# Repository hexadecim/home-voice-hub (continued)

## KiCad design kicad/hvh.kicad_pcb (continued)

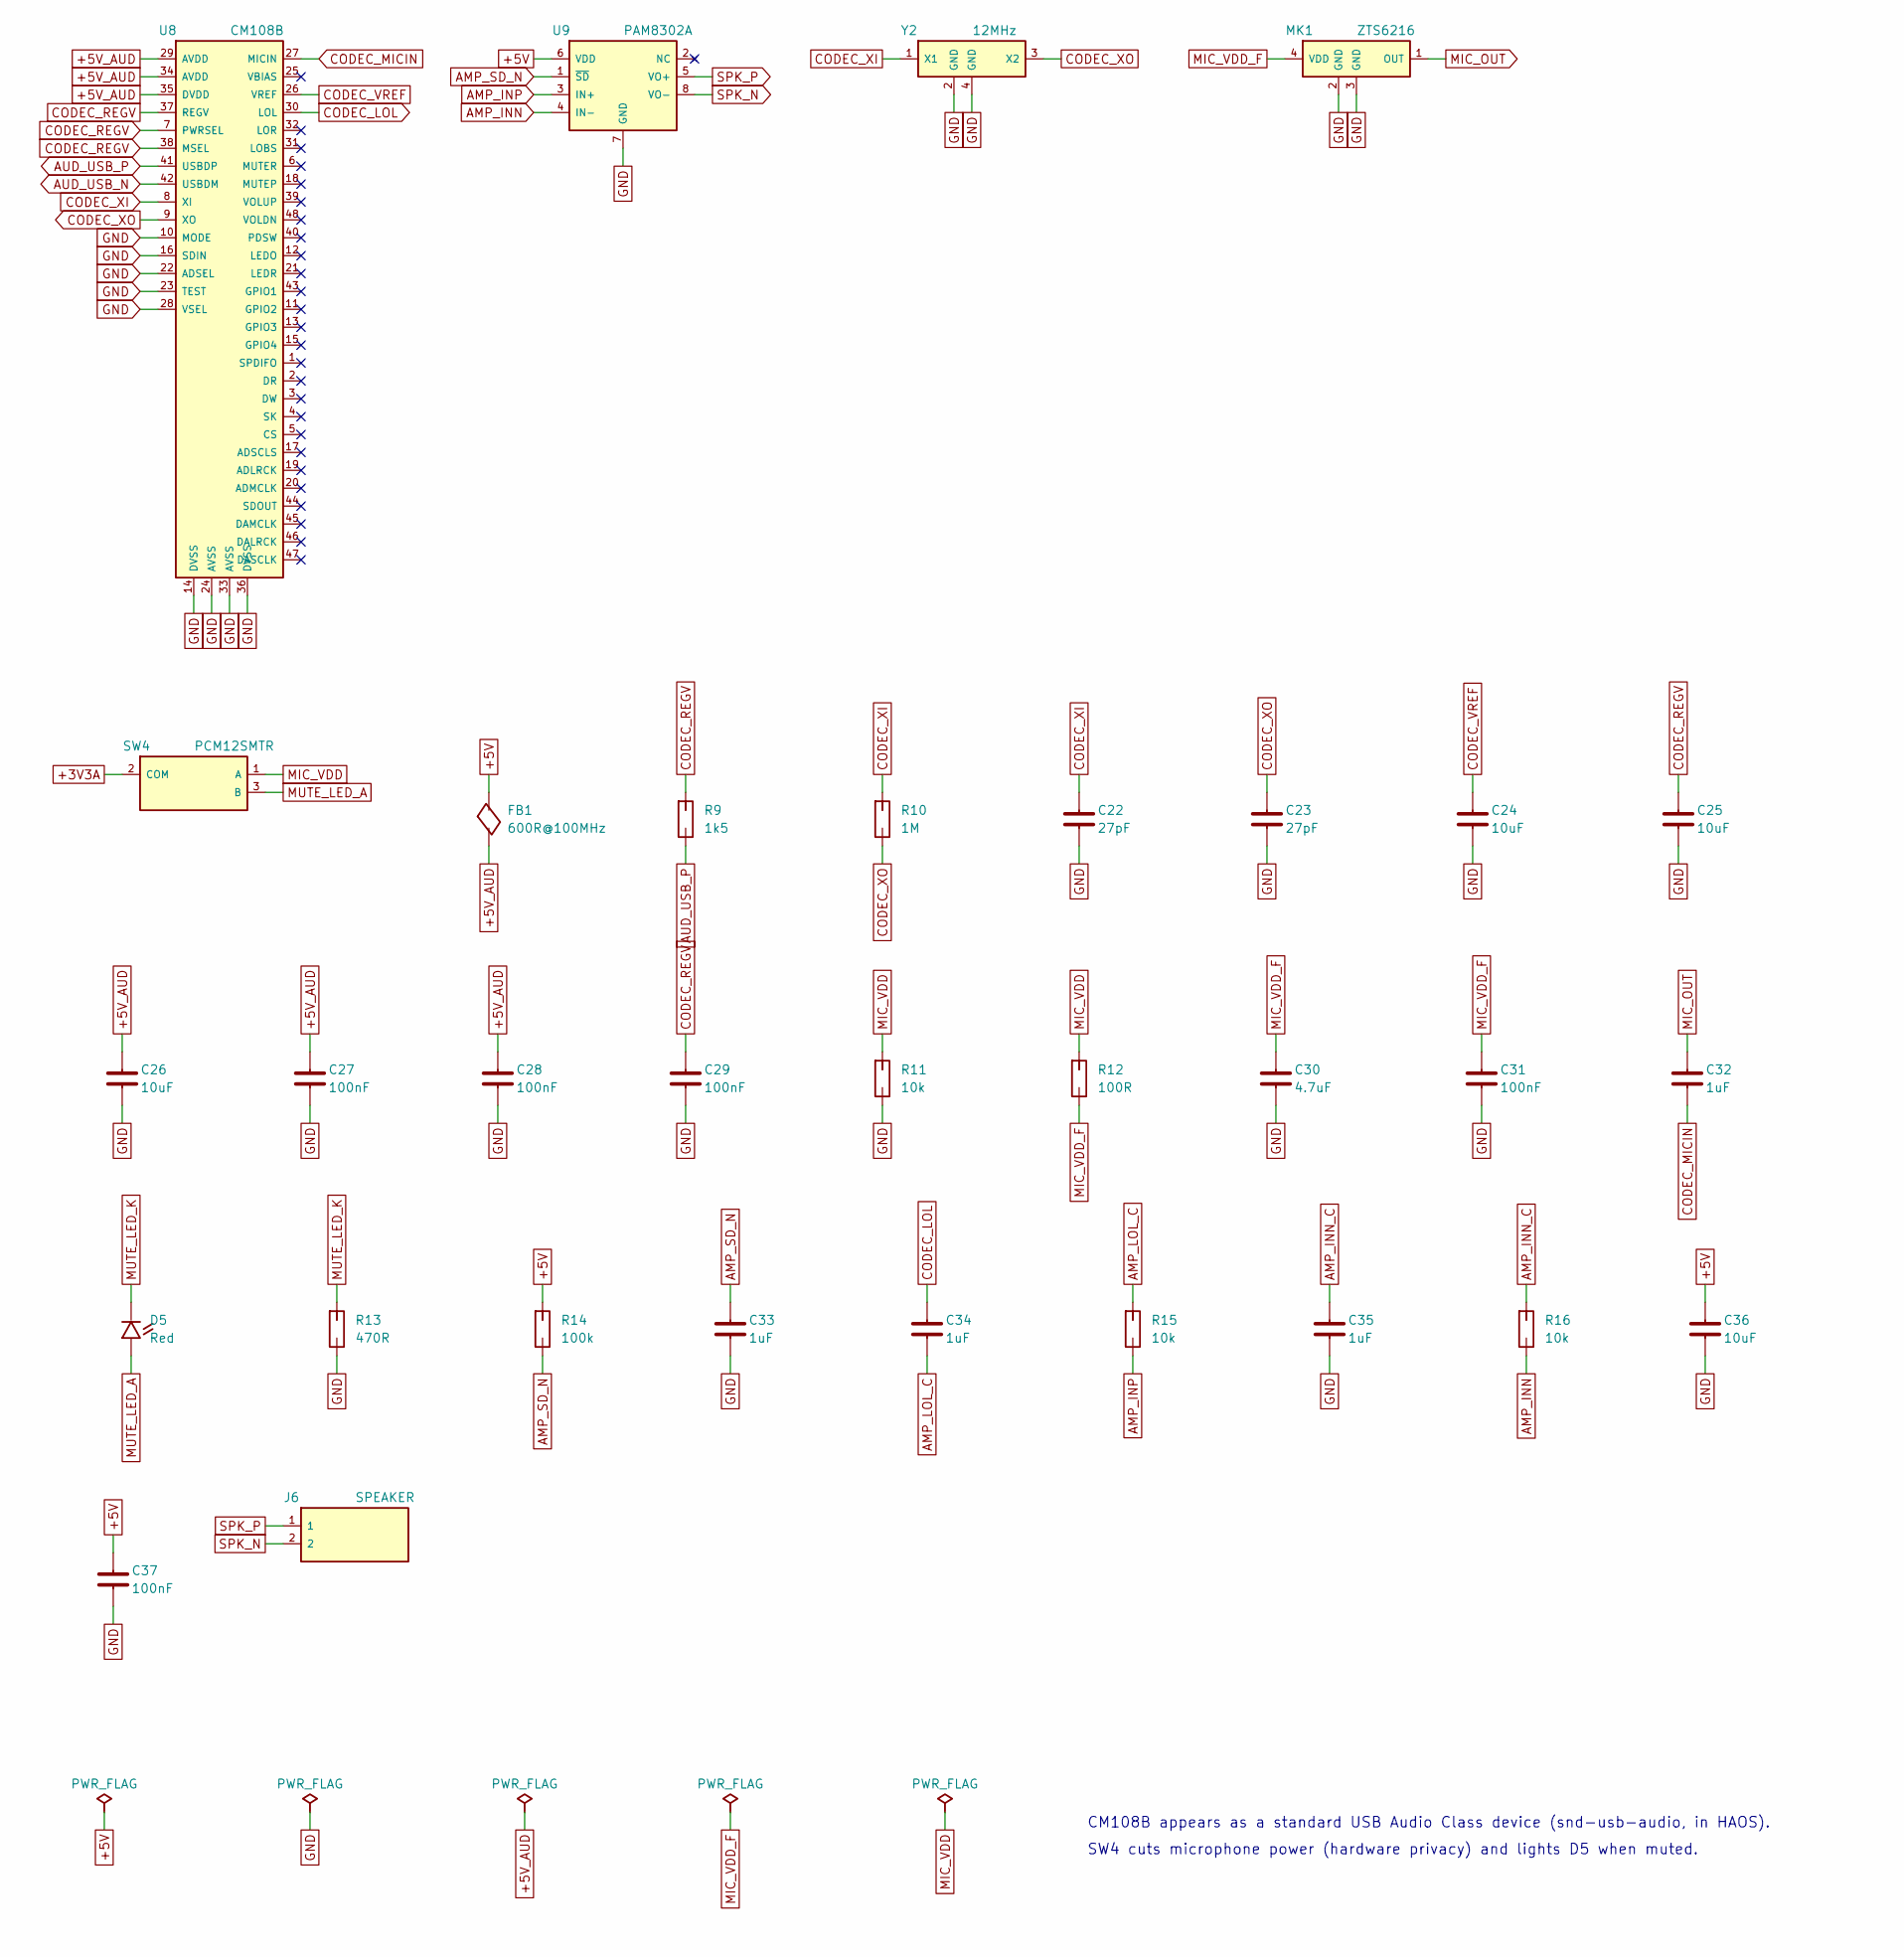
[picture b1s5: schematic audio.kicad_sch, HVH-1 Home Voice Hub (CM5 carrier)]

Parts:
C22, C23: 27pF; C_0402_1005Metric; MPN 0402CG270J500NT; LCSC C1557
C24, C25, C26: 10uF; C_0603_1608Metric; MPN CL10A106KP8NNNC; LCSC C19702
C27, C28, C29, C31, C37: 100nF; C_0402_1005Metric; MPN CL05B104KO5NNNC; LCSC C1525
C30: 4.7uF; C_0603_1608Metric; MPN CL10A475KO8NNNC; LCSC C19666
C32, C33, C34, C35: 1uF; C_0402_1005Metric; MPN CL05A105KA5NQNC; LCSC C52923
C36: 10uF; C_0805_2012Metric; MPN CL21A106KAYNNNE; LCSC C15850
D5: Red; LED_0603_1608Metric; MPN KT-0603R; LCSC C2286
FB1: 600R@100MHz; L_0603_1608Metric; MPN GZ1608D601TF; LCSC C1002
J6: SPEAKER; JST_PH_S2B-PH-K_1x02_P2.00mm_Horizontal; MPN S2B-PH-K-S(LF)(SN); LCSC C173752
MK1: ZTS6216; MIC_ZTS6216; MPN ZTS6216; LCSC C481302
R9: 1k5; R_0402_1005Metric; MPN 0402WGF1501TCE; LCSC C25867
R10: 1M; R_0402_1005Metric; MPN 0402WGF1004TCE; LCSC C26083
R11, R15, R16: 10k; R_0402_1005Metric; MPN 0402WGF1002TCE; LCSC C25744
R12: 100R; R_0402_1005Metric; MPN 0402WGF1000TCE; LCSC C25076
R13: 470R; R_0402_1005Metric; MPN 0402WGF4700TCE; LCSC C25117
R14: 100k; R_0402_1005Metric; MPN 0402WGF1003TCE; LCSC C25741
SW4: PCM12SMTR; SW_SPDT_PCM12; MPN PCM12SMTR; LCSC C221841
U8: CM108B; LQFP-48_7x7mm_P0.5mm; MPN CM108B; LCSC C371347
U9: PAM8302A; MSOP-8_3x3mm_P0.65mm; MPN PAM8302AASCR; LCSC C113367
Y2: 12MHz; Crystal_SMD_3225-4Pin_3.2x2.5mm; MPN X322512MSB4SI; LCSC C9002

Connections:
+3V3A: SW4.2 (COM); also elsewhere on the board
+5V: C36.1, C37.1, FB1.1, R14.1, U9.6 (VDD); also elsewhere on the board
+5V_AUD: C26.1, C27.1, C28.1, FB1.2, U8.29 (AVDD), U8.34 (AVDD), U8.35 (DVDD)
AMP_INN: R16.2, U9.4 (IN-)
AMP_INN_C: C35.1, R16.1
AMP_INP: R15.2, U9.3 (IN+)
AMP_LOL_C: C34.2, R15.1
AMP_SD_N: C33.1, R14.2, U9.1 (~SD)
AUD_USB_N: U8.42 (USBDM); also elsewhere on the board
AUD_USB_P: R9.2, U8.41 (USBDP); also elsewhere on the board
CODEC_LOL: C34.1, U8.30 (LOL)
CODEC_MICIN: C32.2, U8.27 (MICIN)
CODEC_REGV: C25.1, C29.1, R9.1, U8.7 (PWRSEL), U8.37 (REGV), U8.38 (MSEL)
CODEC_VREF: C24.1, U8.26 (VREF)
CODEC_XI: C22.1, R10.1, U8.8 (XI), Y2.1 (X1)
CODEC_XO: C23.1, R10.2, U8.9 (XO), Y2.3 (X2)
GND: C22.2, C23.2, C24.2, C25.2, C26.2, C27.2, C28.2, C29.2, C30.2, C31.2, C33.2, C35.2, C36.2, C37.2, MK1.2 (GND), MK1.3 (GND), R11.2, R13.2, U8.10 (MODE), U8.14 (DVSS), U8.16 (SDIN), U8.22 (ADSEL), U8.23 (TEST), U8.24 (AVSS), U8.28 (VSEL), U8.33 (AVSS), U8.36 (DVSS), U9.7 (GND), Y2.2 (GND), Y2.4 (GND); also elsewhere on the board
MIC_OUT: C32.1, MK1.1 (OUT)
MIC_VDD: R11.1, R12.1, SW4.1 (A)
MIC_VDD_F: C30.1, C31.1, MK1.4 (VDD), R12.2
MUTE_LED_A: D5.2, SW4.3 (B)
MUTE_LED_K: D5.1, R13.1
SPK_N: J6.2, U9.8 (VO-)
SPK_P: J6.1, U9.5 (VO+)

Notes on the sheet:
CM108B appears as a standard USB Audio Class device (snd-usb-audio, in HAOS).
SW4 cuts microphone power (hardware privacy) and lights D5 when muted.

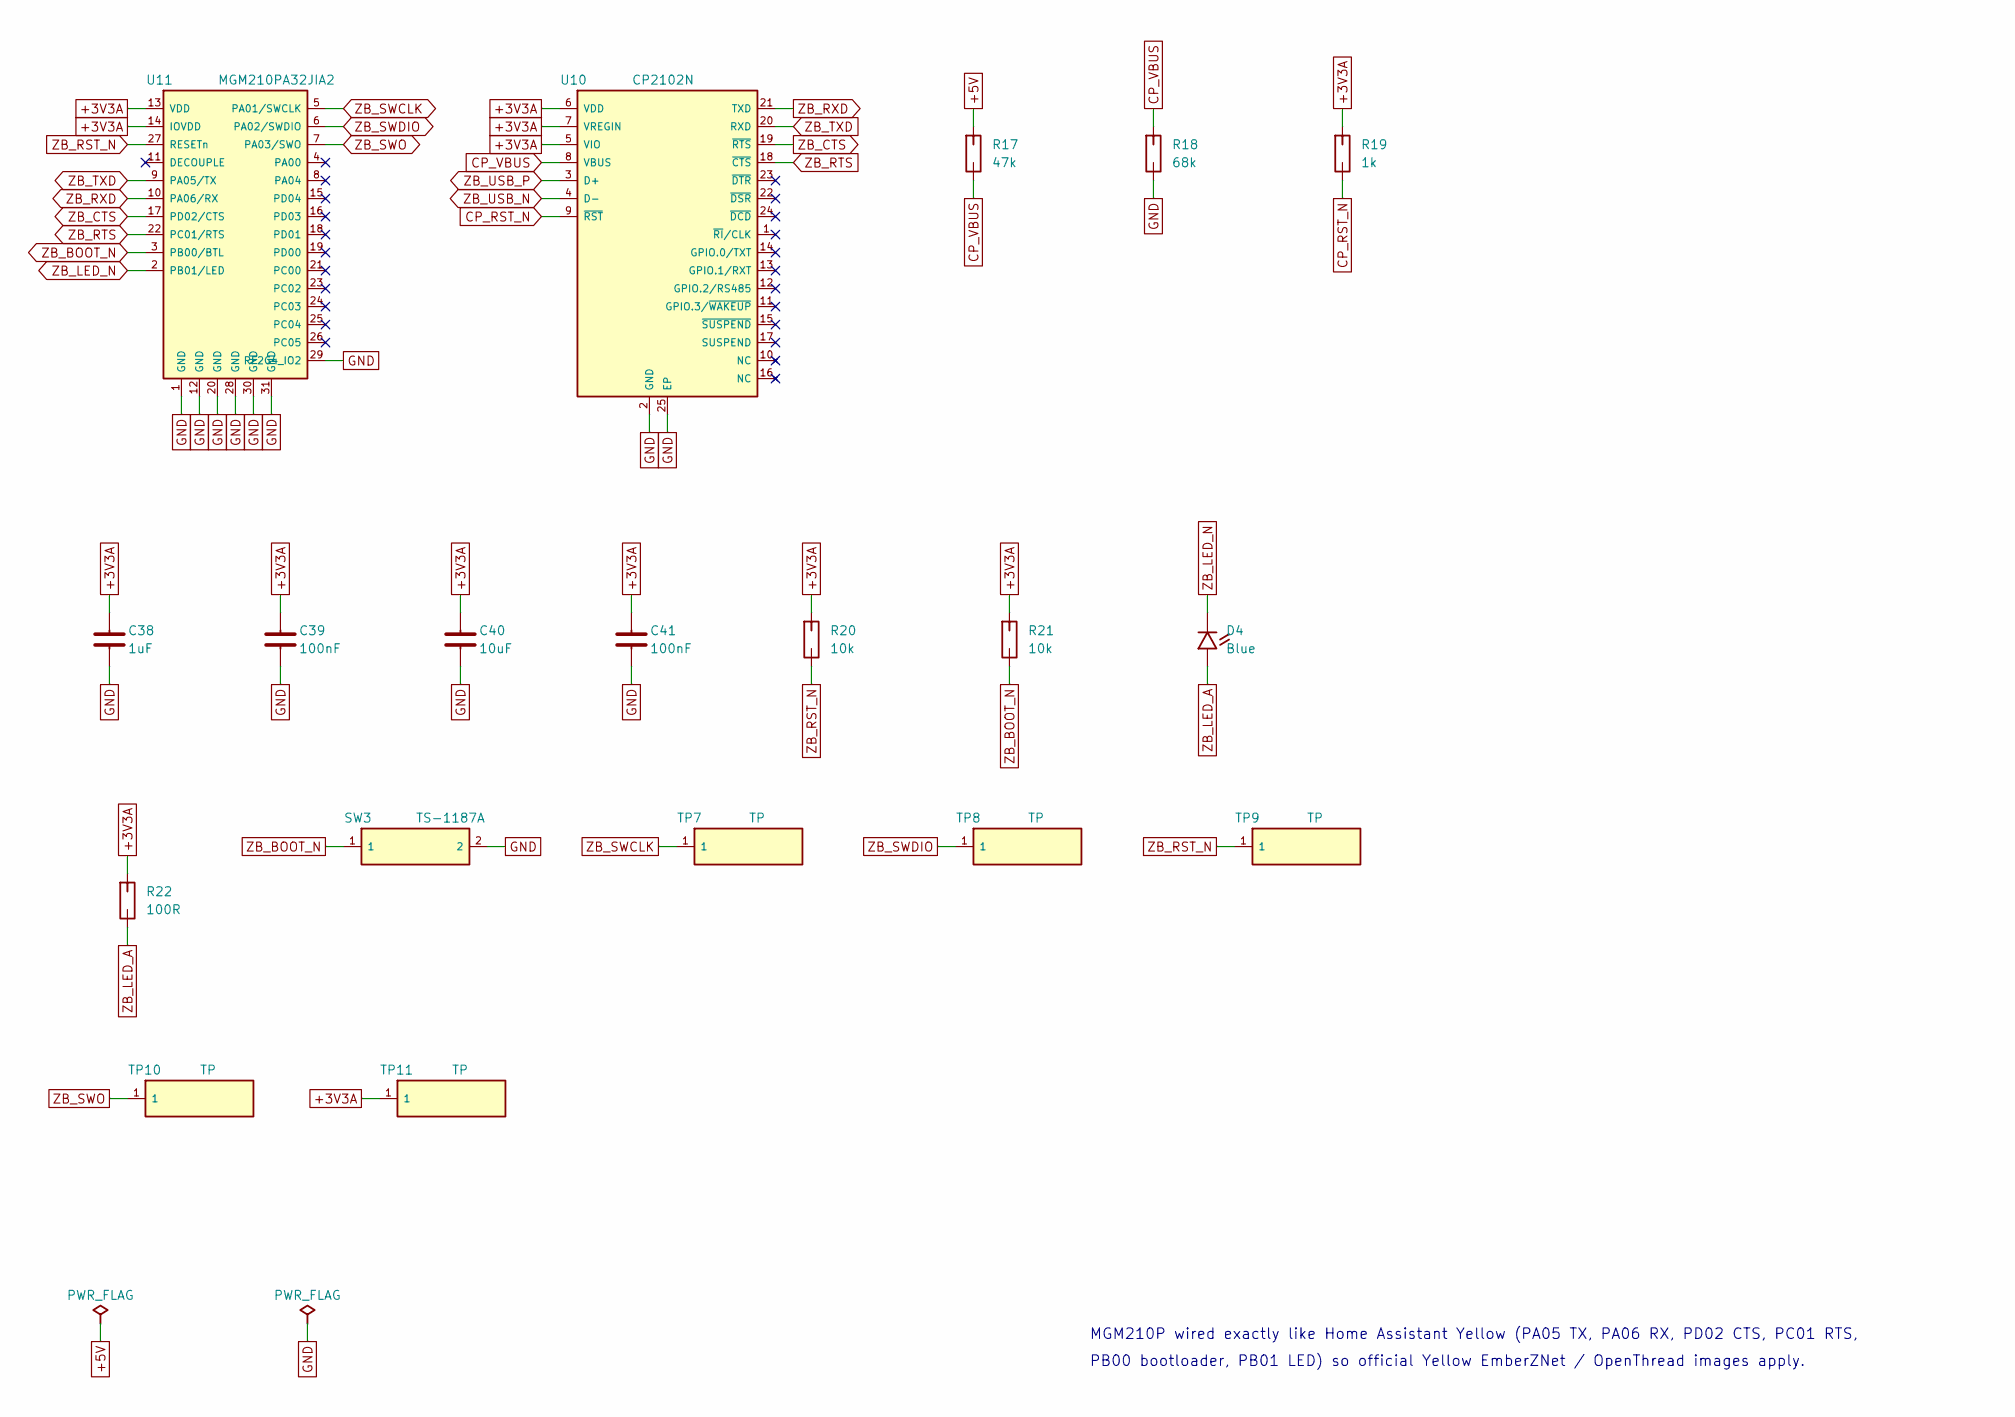
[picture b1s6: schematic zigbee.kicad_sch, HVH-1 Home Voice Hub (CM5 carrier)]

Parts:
C38: 1uF; C_0402_1005Metric; MPN CL05A105KA5NQNC; LCSC C52923
C39, C41: 100nF; C_0402_1005Metric; MPN CL05B104KO5NNNC; LCSC C1525
C40: 10uF; C_0603_1608Metric; MPN CL10A106KP8NNNC; LCSC C19702
D4: Blue; LED_0603_1608Metric; MPN XL-1608UBC-04; LCSC C965807
R17: 47k; R_0402_1005Metric; MPN 0402WGF4702TCE; LCSC C25792
R18: 68k; R_0402_1005Metric; MPN 0402WGF6802TCE; LCSC C36871
R19: 1k; R_0402_1005Metric; MPN 0402WGF1001TCE; LCSC C11702
R20, R21: 10k; R_0402_1005Metric; MPN 0402WGF1002TCE; LCSC C25744
R22: 100R; R_0402_1005Metric; MPN 0402WGF1000TCE; LCSC C25076
SW3: TS-1187A; SW_Push_1P1T_XKB_TS-1187A; MPN TS-1187A-B-A-B; LCSC C318884
TP7, TP8, TP9, TP10, TP11: TP; TestPoint_Pad_D1.0mm
U10: CP2102N; QFN-24-1EP_4x4mm_P0.5mm_EP2.6x2.6mm; MPN CP2102N-A02-GQFN24R; LCSC C969151
U11: MGM210PA32JIA2; SiliconLabs_MGM210P; MPN MGM210PA32JIA2; LCSC C1864147

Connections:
+3V3A: C38.1, C39.1, C40.1, C41.1, R19.1, R20.1, R21.1, R22.1, TP11.1, U10.5 (VIO), U10.6 (VDD), U10.7 (VREGIN), U11.13 (VDD), U11.14 (IOVDD); also elsewhere on the board
+5V: R17.1; also elsewhere on the board
CP_RST_N: R19.2, U10.9 (~RST)
CP_VBUS: R17.2, R18.1, U10.8 (VBUS)
GND: C38.2, C39.2, C40.2, C41.2, R18.2, SW3.2, U10.2 (GND), U10.25 (EP), U11.1 (GND), U11.12 (GND), U11.20 (GND), U11.28 (GND), U11.29 (RF2G4_IO2), U11.30 (GND), U11.31 (GND); also elsewhere on the board
ZB_BOOT_N: R21.2, SW3.1, U11.3 (PB00/BTL)
ZB_CTS: U10.19 (~RTS), U11.17 (PD02/CTS)
ZB_LED_A: D4.2, R22.2
ZB_LED_N: D4.1, U11.2 (PB01/LED)
ZB_RST_N: R20.2, TP9.1, U11.27 (RESETn)
ZB_RTS: U10.18 (~CTS), U11.22 (PC01/RTS)
ZB_RXD: U10.21 (TXD), U11.10 (PA06/RX)
ZB_SWCLK: TP7.1, U11.5 (PA01/SWCLK)
ZB_SWDIO: TP8.1, U11.6 (PA02/SWDIO)
ZB_SWO: TP10.1, U11.7 (PA03/SWO)
ZB_TXD: U10.20 (RXD), U11.9 (PA05/TX)
ZB_USB_N: U10.4 (D-); also elsewhere on the board
ZB_USB_P: U10.3 (D+); also elsewhere on the board

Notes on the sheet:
MGM210P wired exactly like Home Assistant Yellow (PA05 TX, PA06 RX, PD02 CTS, PC01 RTS,
PB00 bootloader, PB01 LED) so official Yellow EmberZNet / OpenThread images apply.

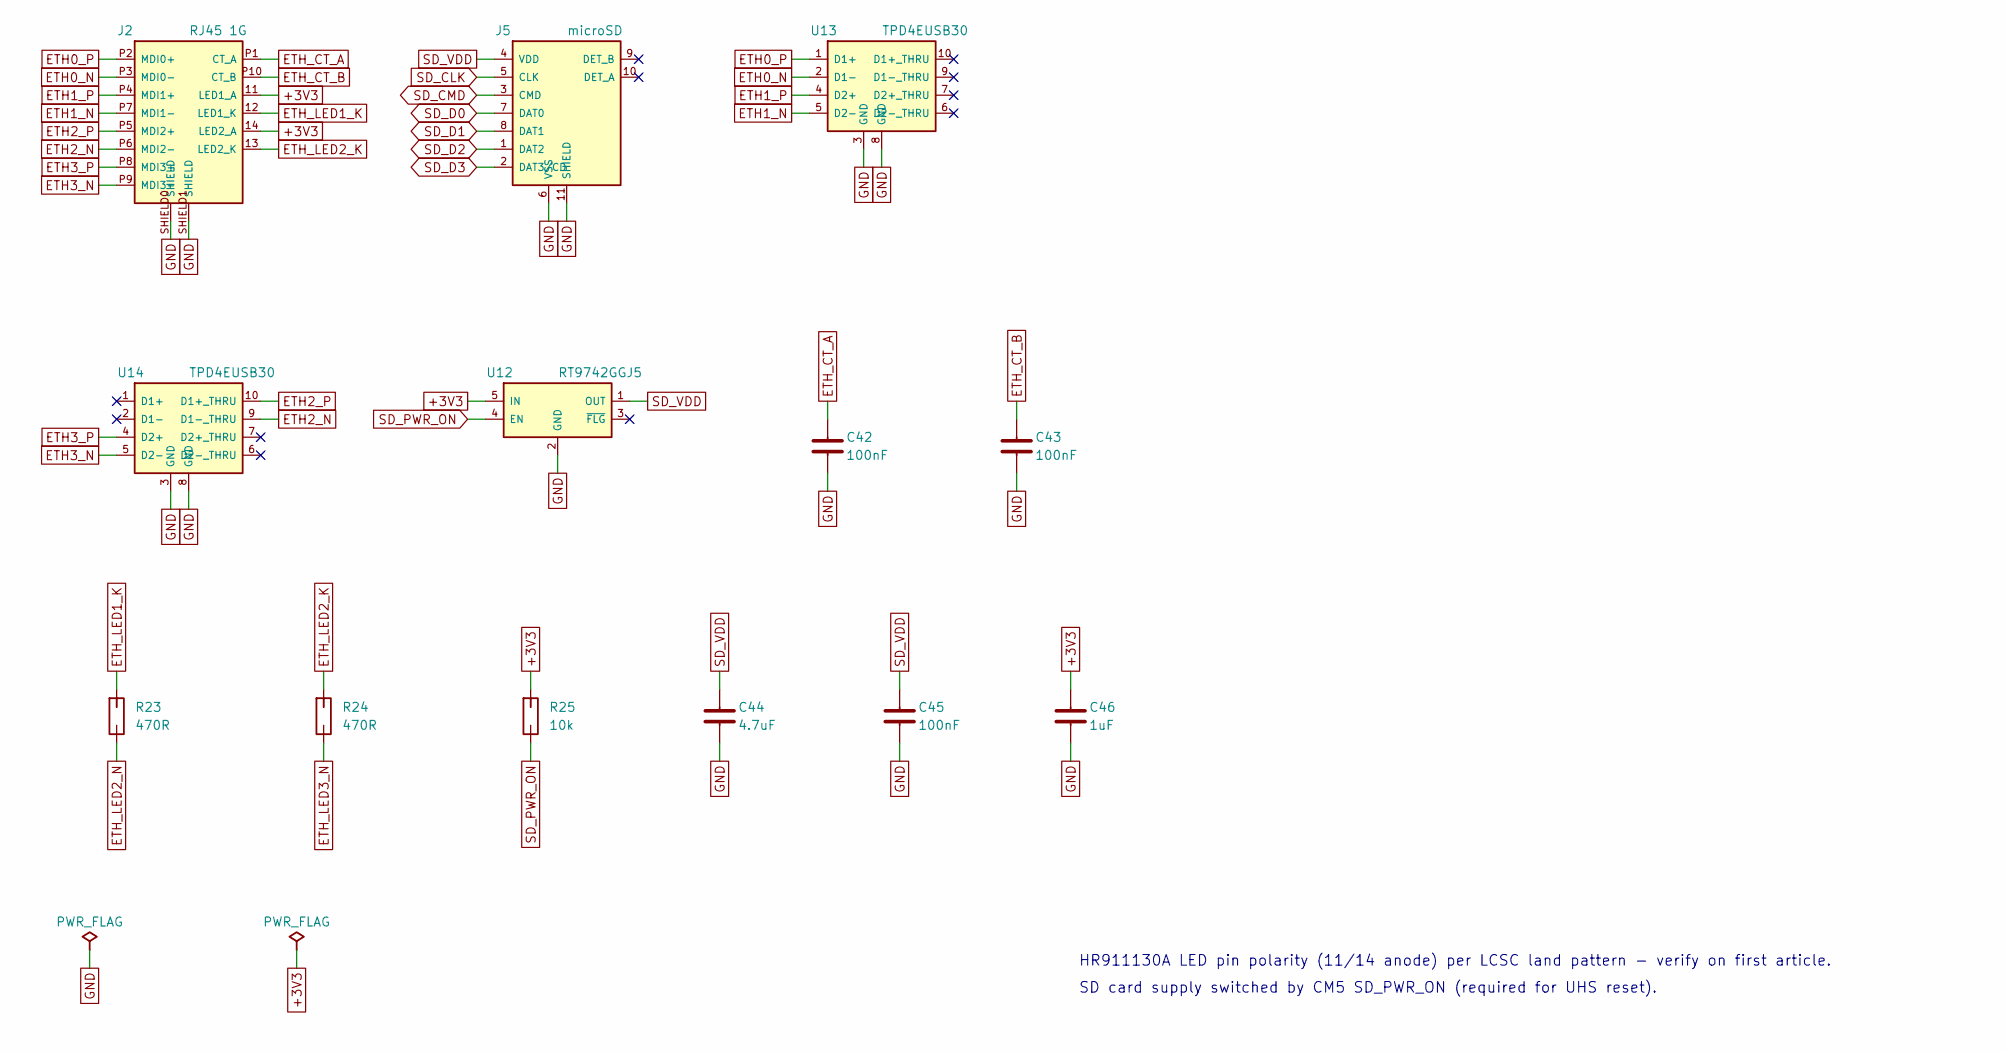
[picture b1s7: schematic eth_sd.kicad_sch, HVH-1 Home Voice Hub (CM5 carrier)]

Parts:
C42, C43, C45: 100nF; C_0402_1005Metric; MPN CL05B104KO5NNNC; LCSC C1525
C44: 4.7uF; C_0603_1608Metric; MPN CL10A475KO8NNNC; LCSC C19666
C46: 1uF; C_0402_1005Metric; MPN CL05A105KA5NQNC; LCSC C52923
J2: RJ45 1G; RJ45_HanRun_HR911130A; MPN HR911130A; LCSC C54408
J5: microSD; microSD_HC_Molex_104031-0811; MPN 1040310811; LCSC C585350
R23, R24: 470R; R_0402_1005Metric; MPN 0402WGF4700TCE; LCSC C25117
R25: 10k; R_0402_1005Metric; MPN 0402WGF1002TCE; LCSC C25744
U12: RT9742GGJ5; SOT-23-5; MPN RT9742GGJ5; LCSC C250547
U13, U14: TPD4EUSB30; USON-10_2.5x1.0mm_P0.5mm; MPN TPD4EUSB30DQAR; LCSC C90627

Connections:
+3V3: C46.1, J2.11 (LED1_A), J2.14 (LED2_A), R25.1, U12.5 (IN); also elsewhere on the board
ETH0_N: J2.P3 (MDI0-), U13.2 (D1-); also elsewhere on the board
ETH0_P: J2.P2 (MDI0+), U13.1 (D1+); also elsewhere on the board
ETH1_N: J2.P7 (MDI1-), U13.5 (D2-); also elsewhere on the board
ETH1_P: J2.P4 (MDI1+), U13.4 (D2+); also elsewhere on the board
ETH2_N: J2.P6 (MDI2-), U14.9 (D1-_THRU); also elsewhere on the board
ETH2_P: J2.P5 (MDI2+), U14.10 (D1+_THRU); also elsewhere on the board
ETH3_N: J2.P9 (MDI3-), U14.5 (D2-); also elsewhere on the board
ETH3_P: J2.P8 (MDI3+), U14.4 (D2+); also elsewhere on the board
ETH_CT_A: C42.1, J2.P1 (CT_A)
ETH_CT_B: C43.1, J2.P10 (CT_B)
ETH_LED1_K: J2.12 (LED1_K), R23.1
ETH_LED2_K: J2.13 (LED2_K), R24.1
ETH_LED2_N: R23.2; also elsewhere on the board
ETH_LED3_N: R24.2; also elsewhere on the board
GND: C42.2, C43.2, C44.2, C45.2, C46.2, J2.SHIELD0 (SHIELD), J2.SHIELD1 (SHIELD), J5.6 (VSS), J5.11 (SHIELD), U12.2 (GND), U13.3 (GND), U13.8 (GND), U14.3 (GND), U14.8 (GND); also elsewhere on the board
SD_CLK: J5.5 (CLK); also elsewhere on the board
SD_CMD: J5.3 (CMD); also elsewhere on the board
SD_D0: J5.7 (DAT0); also elsewhere on the board
SD_D1: J5.8 (DAT1); also elsewhere on the board
SD_D2: J5.1 (DAT2); also elsewhere on the board
SD_D3: J5.2 (DAT3/CD); also elsewhere on the board
SD_PWR_ON: R25.2, U12.4 (EN); also elsewhere on the board
SD_VDD: C44.1, C45.1, J5.4 (VDD), U12.1 (OUT); also elsewhere on the board

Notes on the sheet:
HR911130A LED pin polarity (11/14 anode) per LCSC land pattern - verify on first article.
SD card supply switched by CM5 SD_PWR_ON (required for UHS reset).

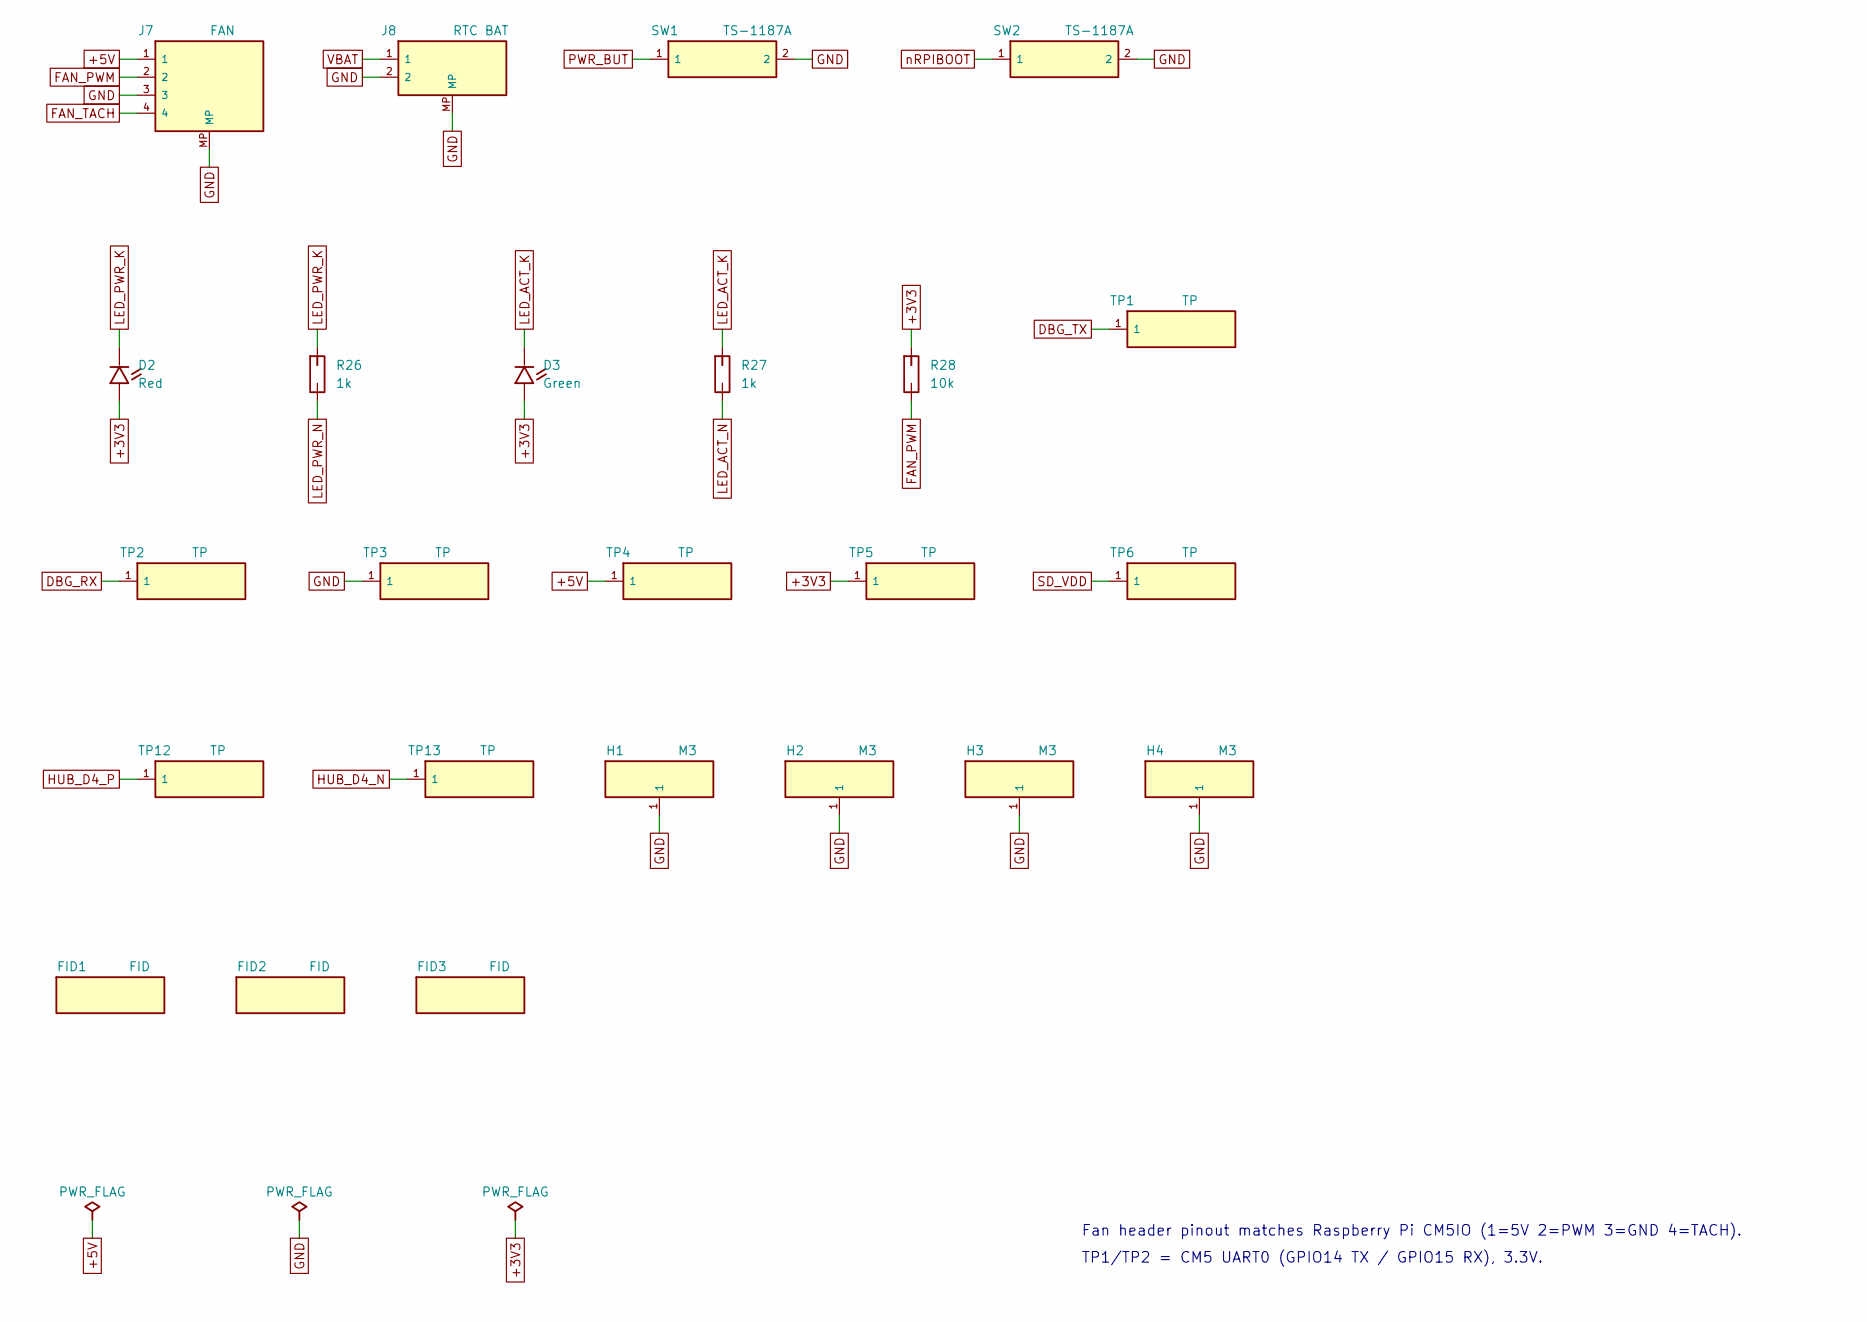
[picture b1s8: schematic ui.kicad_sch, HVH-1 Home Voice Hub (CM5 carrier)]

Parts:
D2: Red; LED_0603_1608Metric; MPN KT-0603R; LCSC C2286
D3: Green; LED_0603_1608Metric; MPN XL-1608UGC-04; LCSC C965804
FID1, FID2, FID3: FID; Fiducial_1mm_Mask2mm
H1, H2, H3, H4: M3; MountingHole_3.2mm_M3_Pad_Via
J7: FAN; JST_SH_SM04B-SRSS-TB_1x04-1MP_P1.00mm_Horizontal; MPN SM04B-SRSS-TB(LF)(SN); LCSC C160404
J8: RTC BAT; JST_SH_SM02B-SRSS-TB_1x02-1MP_P1.00mm_Horizontal; MPN SM02B-SRSS-TB(LF)(SN); LCSC C160402
R26, R27: 1k; R_0402_1005Metric; MPN 0402WGF1001TCE; LCSC C11702
R28: 10k; R_0402_1005Metric; MPN 0402WGF1002TCE; LCSC C25744
SW1, SW2: TS-1187A; SW_Push_1P1T_XKB_TS-1187A; MPN TS-1187A-B-A-B; LCSC C318884
TP1, TP2, TP3, TP4, TP5, TP6, TP12, TP13: TP; TestPoint_Pad_D1.0mm

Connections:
+3V3: D2.2, D3.2, R28.1, TP5.1; also elsewhere on the board
+5V: J7.1, TP4.1; also elsewhere on the board
DBG_RX: TP2.1; also elsewhere on the board
DBG_TX: TP1.1; also elsewhere on the board
FAN_PWM: J7.2, R28.2; also elsewhere on the board
FAN_TACH: J7.4; also elsewhere on the board
GND: H1.1, H2.1, H3.1, H4.1, J7.3, J7.MP, J8.2, J8.MP, SW1.2, SW2.2, TP3.1; also elsewhere on the board
HUB_D4_N: TP13.1; also elsewhere on the board
HUB_D4_P: TP12.1; also elsewhere on the board
LED_ACT_K: D3.1, R27.1
LED_ACT_N: R27.2; also elsewhere on the board
LED_PWR_K: D2.1, R26.1
LED_PWR_N: R26.2; also elsewhere on the board
PWR_BUT: SW1.1; also elsewhere on the board
SD_VDD: TP6.1; also elsewhere on the board
VBAT: J8.1; also elsewhere on the board
nRPIBOOT: SW2.1; also elsewhere on the board

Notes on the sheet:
Fan header pinout matches Raspberry Pi CM5IO (1=5V 2=PWM 3=GND 4=TACH).
TP1/TP2 = CM5 UART0 (GPIO14 TX / GPIO15 RX), 3.3V.

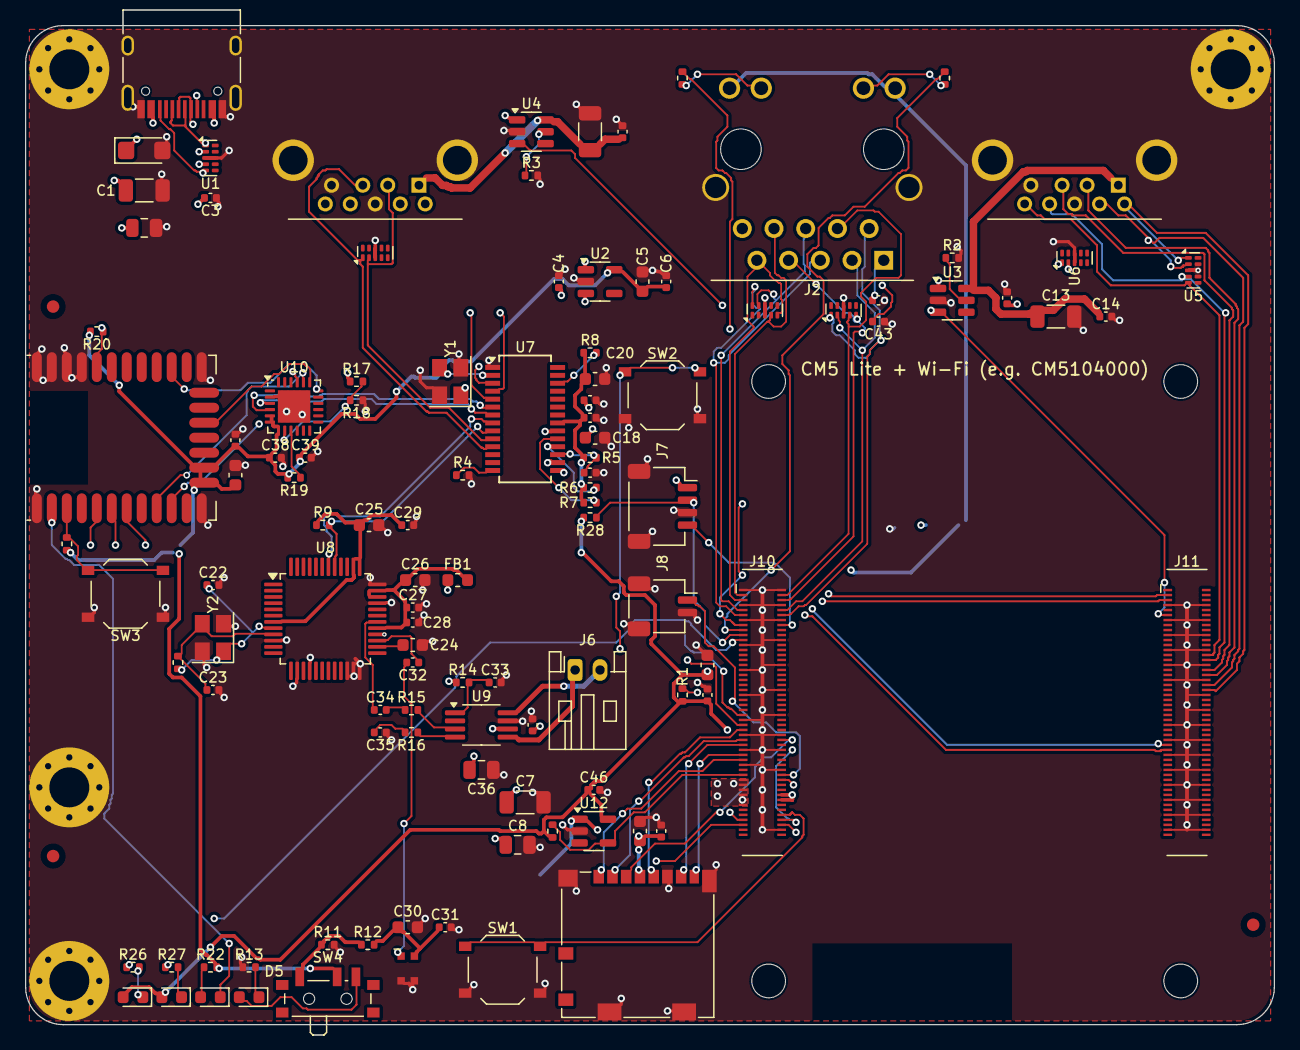
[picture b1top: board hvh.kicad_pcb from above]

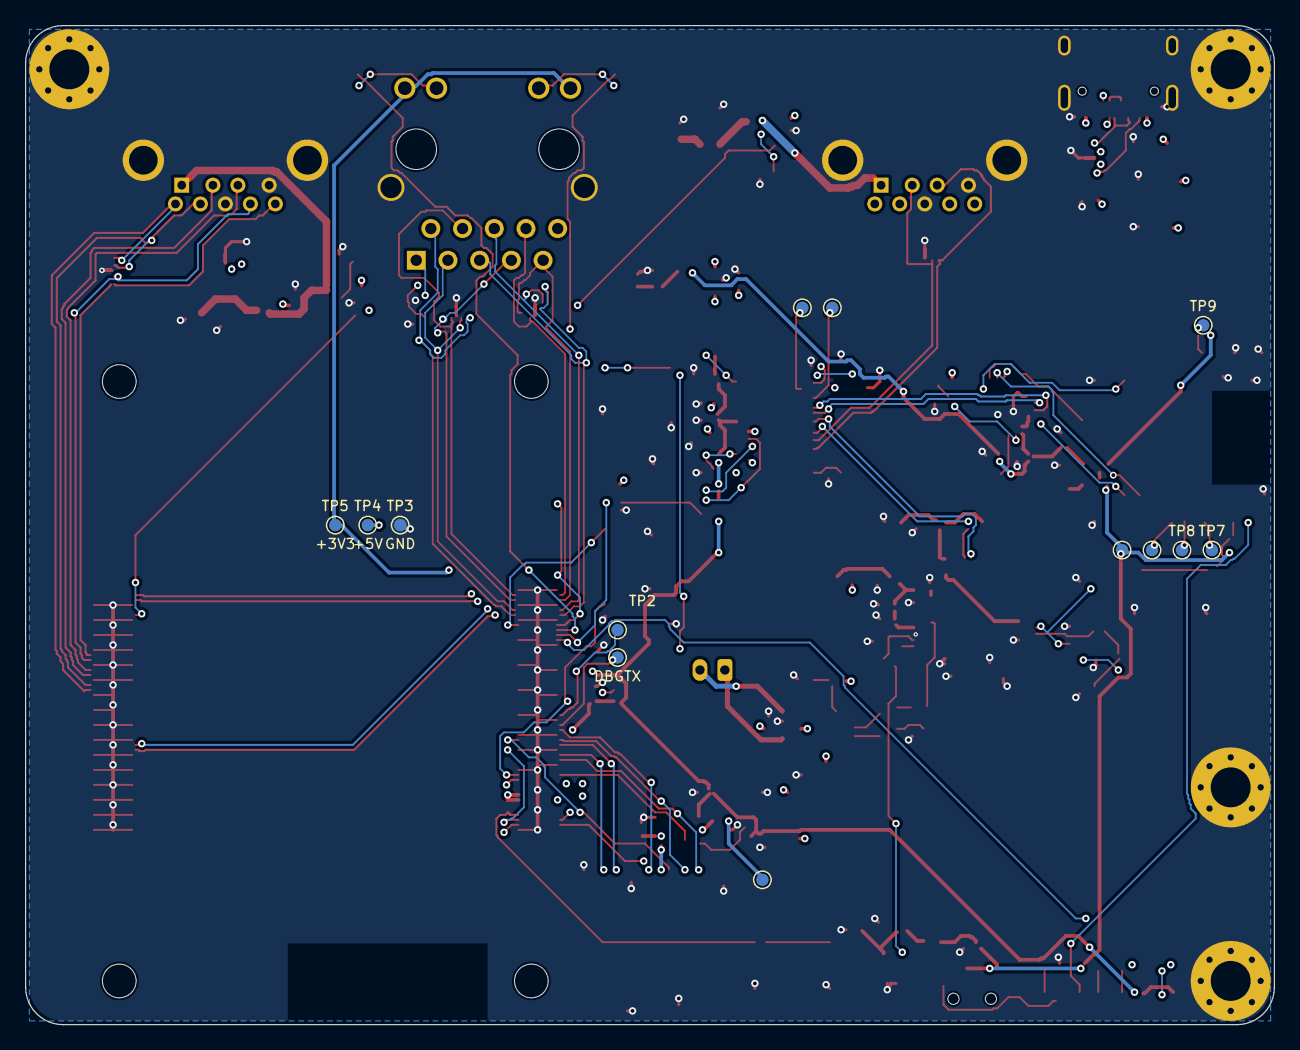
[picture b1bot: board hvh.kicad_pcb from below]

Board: 6 copper layers, 100.0 x 80.0 mm, 132 parts (13 on the bottom side), 103 nets.

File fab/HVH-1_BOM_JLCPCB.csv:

Comment,Designator,Footprint,LCSC Part #
USB-C PWR,J1,USB_C_Receptacle_HRO_TYPE-C-31-M-12,C165948
SMF5.0A,D1,D_SMF,C193402
47uF,"C1,C7,C13,C15",C_1206_3216Metric,C68361
22uF,C2,C_0805_2012Metric,C45783
100nF,"C3,C6,C11,C14,C16,C19,C21,C27,C28,C29,C31,C37,C39,C41,C42,C43,C45",C_0402_1005Metric,C1525
TPD4EUSB30,"U1,U5,U6,U13,U14,U15",USON-10_2.5x1.0mm_P0.5mm,C90627
TLV75533P,U2,SOT-23-5,C404027
1uF,"C4,C12,C17,C32,C33,C34,C35,C38,C46",C_0402_1005Metric,C52923
4.7uF,"C5,C10,C20,C30,C44",C_0603_1608Metric,C19666
DF40C-100DS,"J10,J11",CM5_DF40C-100DS-0.4V,C597931
0R,R1,R_0402_1005Metric,C17168
10uF,"C8,C36",C_0805_2012Metric,C15850
USB-A,"J3,J4",USB3_A_Amphenol_GSB311131HR,C473057
TPS2553,"U3,U4",SOT-23-6,C55266
26k1 1%,"R2,R3",R_0402_1005Metric,C155697
FE1.1s,U7,SSOP-28_3.9x9.9mm_P0.635mm,C9359
12MHz,"Y1,Y2",Crystal_SMD_3225-4Pin_3.2x2.5mm,C9002
2k7 1%,R4,R_0402_1005Metric,C25885
10k,"R5,R6,R7,R8,R11,R15,R16,R20,R21,R25,R28",R_0402_1005Metric,C25744
10uF,"C18,C24,C25,C26,C40",C_0603_1608Metric,C19702
600R@100MHz,FB1,L_0603_1608Metric,C1002
CM108B,U8,LQFP-48_7x7mm_P0.5mm,C371347
1k5,R9,R_0402_1005Metric,C25867
1M,R10,R_0402_1005Metric,C26083
27pF,"C22,C23",C_0402_1005Metric,C1557
PCM12SMTR,SW4,SW_SPDT_PCM12,C221841
100R,"R12,R22",R_0402_1005Metric,C25076
ZTS6216,MK1,MIC_ZTS6216,C481302
Red,"D2,D5",LED_0603_1608Metric,C2286
470R,"R13,R23,R24",R_0402_1005Metric,C25117
PAM8302A,U9,MSOP-8_3x3mm_P0.65mm,C113367
100k,R14,R_0402_1005Metric,C25741
SPEAKER,J6,JST_PH_S2B-PH-K_1x02_P2.00mm_Horizontal,C173752
CP2102N,U10,QFN-24-1EP_4x4mm_P0.5mm_EP2.6x2.6mm,C969151
47k,R17,R_0402_1005Metric,C25792
68k,R18,R_0402_1005Metric,C36871
1k,"R19,R26,R27",R_0402_1005Metric,C11702
MGM210PA32JIA2,U11,SiliconLabs_MGM210P,C1864147
Blue,D4,LED_0603_1608Metric,C965807
TS-1187A,"SW1,SW2,SW3",SW_Push_1P1T_XKB_TS-1187A,C318884
RJ45 1G,J2,RJ45_HanRun_HR911130A,C54408
microSD,J5,microSD_HC_Molex_104031-0811,C585350
RT9742GGJ5,U12,SOT-23-5,C250547
Green,D3,LED_0603_1608Metric,C965804
FAN,J7,JST_SH_SM04B-SRSS-TB_1x04-1MP_P1.00mm_Horizontal,C160404
RTC BAT,J8,JST_SH_SM02B-SRSS-TB_1x02-1MP_P1.00mm_Horizontal,C160402

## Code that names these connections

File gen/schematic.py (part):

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            "port 3 = Zigbee USB-UART, port 4 = test pads. FE1.1s has internal crystal load caps."],
    "audio": ["CM108B appears as a standard USB Audio Class device (snd-usb-audio, in HAOS).",
              "SW4 cuts microphone power (hardware privacy) and lights D5 when muted."],
    "zigbee": ["MGM210P wired exactly like Home Assistant Yellow (PA05 TX, PA06 RX, PD02 CTS, PC01 RTS,",
               "PB00 bootloader, PB01 LED) so official Yellow EmberZNet / OpenThread images apply."],
    "eth_sd": ["HR911130A LED pin polarity (11/14 anode) per LCSC land pattern - verify on first article.",
               "SD card supply switched by CM5 SD_PWR_ON (required for UHS reset)."],
    "ui": ["Fan header pinout matches Raspberry Pi CM5IO (1=5V 2=PWM 3=GND 4=TACH).",
           "TP1/TP2 = CM5 UART0 (GPIO14 TX / GPIO15 RX), 3.3V."],
}

def gen_root(papers):
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
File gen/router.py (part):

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ALL = list(range(NL))
OUTER_ONLY = {"USB3", "ETH", "USB3_FAT", "ETH_FAT", "VBUS", "SPK", "P5V"}   # USB2 may use In2 (stripline, 90R target)
PAIR_PITCH = 0.40
NOFAT = {"USB3A_DP", "USB3A_DN"}   # pins sit in separate gaps of the USB3-A SS pin row
HIGH_SPEED = {"USB2", "USB3", "ETH"}

def L2(v): return pcbnew.ToMM(v)
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        print(f"pair {name}: {'ok' if ok else 'FAIL'} {time.time() - t0:.1f}s", flush=True)
        done |= {p, n}
    first = ["SD_PWR_ON", "SD_D2", "SD_D1", "SD_D0", "SD_CMD", "SD_D3", "SD_CLK", "SD_VDD",
             "CC1", "CC2", "VBAT", "PWR_BUT", "GPIO_VREF", "FAN_TACH", "ETH_LED2_N", "ETH_LED3_N",
             "DBG_RX", "DBG_TX", "ZB_TXD", "ZB_RXD", "ZB_SWDIO", "ZB_SWCLK", "ZB_SWO", "ZB_RST_N", "ZB_CTS", "ZB_RTS",
             "HUB_D4_P", "HUB_D4_N", "CP_VBUS", "LED_ACT_N", "VBUS_EN", "FAN_PWM", "HUB_XOUT", "HUB_XIN", "CP_RST_N"]
    for n in first:
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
